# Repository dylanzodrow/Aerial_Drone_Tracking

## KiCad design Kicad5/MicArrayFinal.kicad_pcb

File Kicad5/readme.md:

Hopefully, the final pcb designs. In this iteration the microphones are on breakout boards and the traces are enlarged to ensure proper insulation when manufactured.

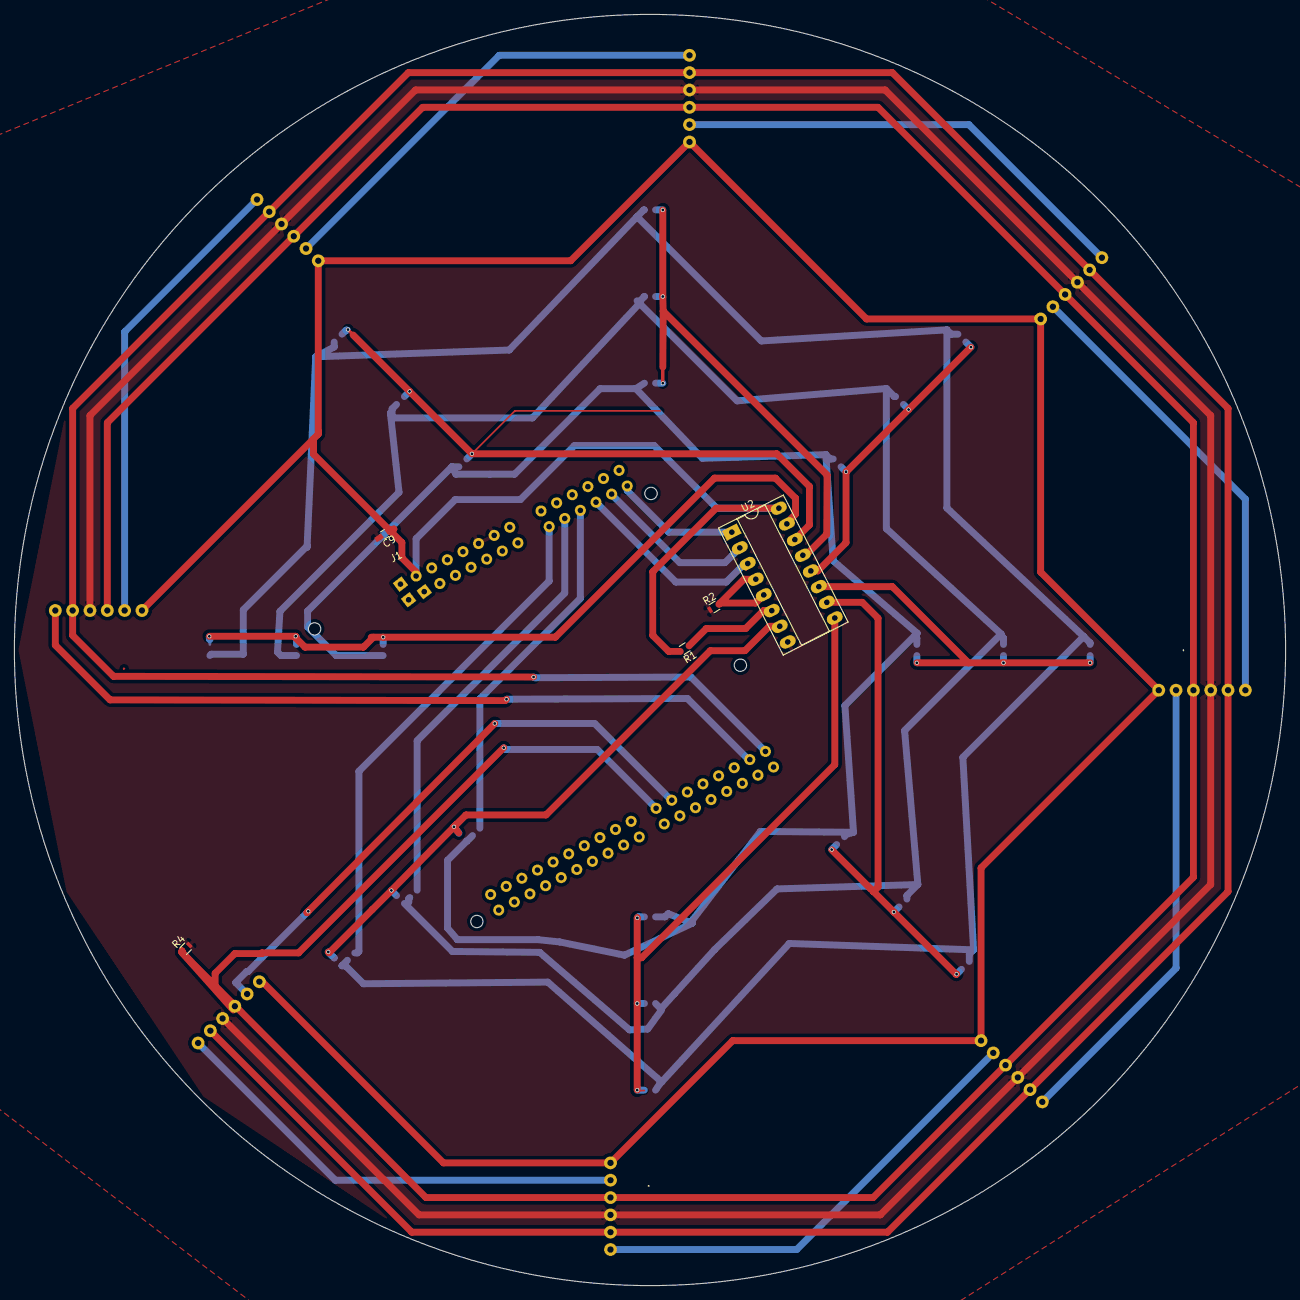
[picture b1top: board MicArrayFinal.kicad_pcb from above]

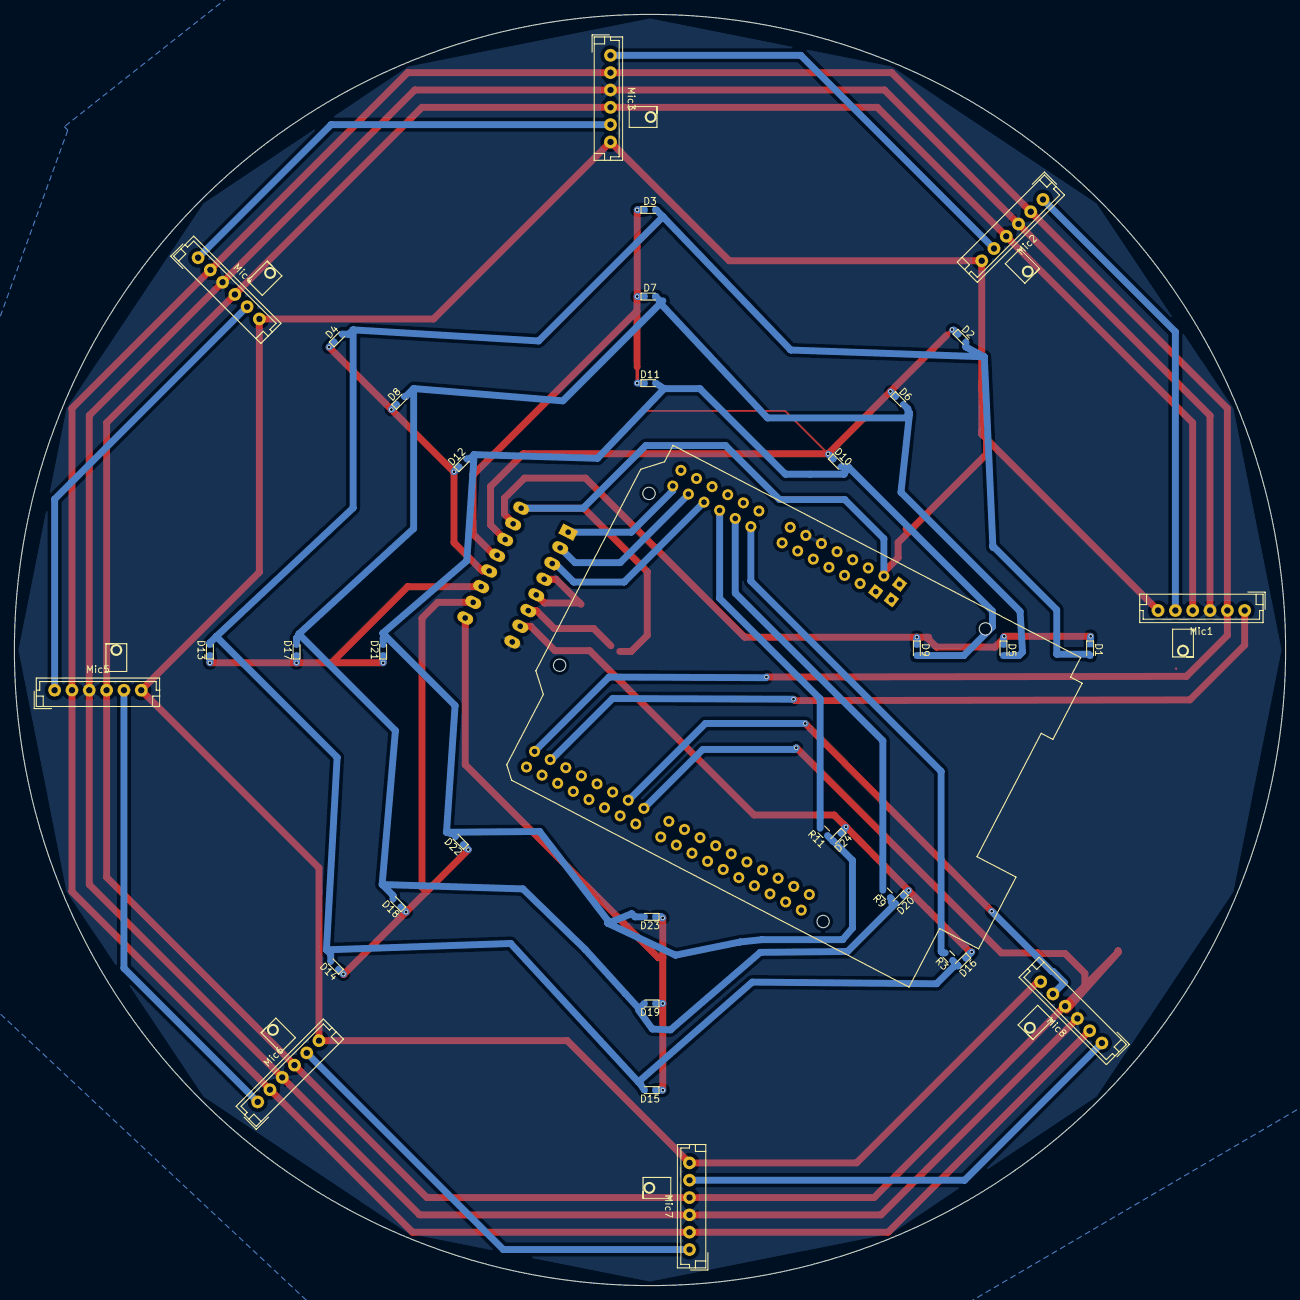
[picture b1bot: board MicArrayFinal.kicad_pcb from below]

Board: 2 copper layers, 183.4 x 183.4 mm, 41 parts (35 on the bottom side), 32 nets.

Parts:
C9: 10uF; C_0603_HandSoldering
D1, D2, D3, D4, D5, D6, D7, D8, D9, D10, D11, D12, D13, D14, D15, D16, D17, D18, D19, D20, D21, D22, D23, D24: LED; LED_0603
J1: Conn_01x12_Male; ArduinoLike
Mic1, Mic2, Mic3, Mic4, Mic5, Mic6, Mic7, Mic8: ICS-52000; MicBoard
R1, R2: 1k; R_0603
R3, R9, R11: 100; R_0603
R4: 100k; R_0603
U2: SN74HC138; DIP-16_W7.62mm_Socket_LongPads

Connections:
+3V3: C9.1, J1.1, Mic1.2, Mic2.2, Mic3.2, Mic4.2, Mic5.2, Mic6.2, Mic7.2, Mic8.2, R1.2, U2.16
/Clock: J1.3, Mic1.6, Mic2.6, Mic3.6, Mic4.6, Mic5.6, Mic6.6, Mic7.6, Mic8.6
/LEDArray/ColSelectA: J1.10, R3.2
/LEDArray/ColSelectB: J1.11, R9.2
/LEDArray/ColSelectC: J1.12, R11.2
/LEDArray/LEDSA: D1.2, D2.2, D3.2, D4.2, D13.2, D14.2, D15.2, D16.2, R3.1
/LEDArray/LEDSB: D5.2, D6.2, D7.2, D8.2, D17.2, D18.2, D19.2, D20.2, R9.1
/LEDArray/LEDSC: D9.2, D10.2, D11.2, D12.2, D21.2, D22.2, D23.2, D24.2, R11.1
/LEDArray/Row1: D1.1, D5.1, D9.1, U2.15
/LEDArray/Row2: D2.1, D6.1, D10.1, U2.14
/LEDArray/Row3: D3.1, D7.1, D11.1, U2.13
/LEDArray/Row4: D4.1, D8.1, D12.1, U2.12
/LEDArray/Row5: D13.1, D17.1, D21.1, U2.11
/LEDArray/Row6: D14.1, D18.1, D22.1, U2.10
/LEDArray/Row7: D15.1, D19.1, D23.1, U2.9
/LEDArray/Row8: D16.1, D20.1, D24.1, U2.7
/LEDArray/RowSelectA: J1.7, U2.1
/LEDArray/RowSelectB: J1.8, U2.2
/LEDArray/RowSelectC: J1.9, U2.3
/SerialData: J1.5, Mic1.7, Mic2.7, Mic3.7, Mic4.7, Mic5.7, Mic6.7, Mic7.7, Mic8.7, R4.1
/WISO: J1.6, Mic8.1
/WS: J1.4, Mic1.5
GND: C9.2, J1.2, Mic1.4, Mic2.4, Mic3.4, Mic4.4, Mic5.4, Mic6.4, Mic7.4, Mic8.4, R2.2, R4.2, U2.8
unnamed: Mic1.1, Mic2.5
unnamed: Mic2.1, Mic3.5
unnamed: Mic3.1, Mic4.5
unnamed: Mic4.1, Mic5.5
unnamed: Mic5.1, Mic6.5
unnamed: Mic6.1, Mic7.5
unnamed: Mic7.1, Mic8.5
unnamed: R1.1, U2.6
unnamed: R2.1, U2.4, U2.5

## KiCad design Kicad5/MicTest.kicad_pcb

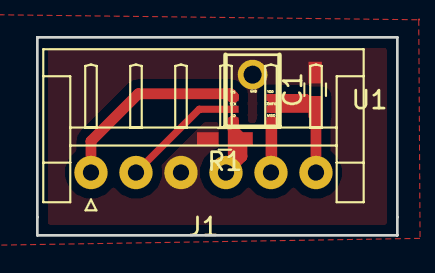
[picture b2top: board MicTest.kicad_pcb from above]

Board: 2 copper layers, 20.0 x 11.0 mm, 4 parts (0 on the bottom side), 6 nets.

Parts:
C1: C; C_0603_HandSoldering
J1: Conn_01x06; JST_EH_S06B-EH_06x2.50mm_Angled
R1: R; C_0603_HandSoldering
U1: ICS 52000; ICS25000labels

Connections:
GND: C1.2, J1.6, R1.2, U1.4
unnamed: C1.1, J1.1, U1.2, U1.3
unnamed: J1.2, U1.5
unnamed: J1.3, U1.6
unnamed: J1.4, R1.1, U1.7
unnamed: J1.5, U1.1

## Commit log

2018-02-01 Im learning about WAV files
2018-02-01 Rename WAV Viewer to WAVviewer
2018-02-01 Rename WAVviewer to WAVviewer.html
2018-02-01 Information we gathered so far
2018-02-01 Add files via upload
    These are audio recordings of the drone on a table top at 0.5m
2018-02-02 Recorded with my Tablet
2018-02-02 KiKax Schematics and PCB layout
2018-02-04 Add files via upload
    These are the audio recordings of the drone. All of these recordings were made using Dr. Siderius' microphone array and the Ishmael software. The two file names beginning with "sound" are recordings 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
    File names beginning in 1, 2, 3, or 4 indicate a recording taken at the specified distance from the center of the microphone pair with the drone operating at its "hover" program.
    File names beginning in 0, 45, 135, or 180 indicate a recording taken at 4m distance at the angle indicated measured from the plane of the two microphones (IE 0 degrees indicates the meas
2018-02-15 Create Audio2
2018-03-01 Add files via upload
    Documents for the DSP.
    Included are the data sheet for the microcontroller itself, the user guide for the dev kit, and a tutorial on downloading the DSP library to the dev kit.
2018-03-01 Create Read me
2018-04-26 Add files via upload
    These files were created as if the drone was in front of mic 1 inline with mic 5. The delays are 0, 0.012, 0.035, 0.046, and 0.070 seconds.
2018-04-30 Create LEDTest.txt
    A test progtam for the LEDs
